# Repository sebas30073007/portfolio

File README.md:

# Portafolio — Sebastián Méndez Villegas (SMV)

Portafolio personal de proyectos de ingeniería mecatrónica y sistemas
ciberfísicos. Hecho con **HTML, CSS y JavaScript** (sin frameworks), listo para
publicar en **GitHub Pages**. Diseño base tomado de `assets/docs/portfolio SMV.pdf`.

## Estructura

```
portfolio/
├── index.html              # Home: feed de proyectos (búsqueda + filtro), sin hero
├── featured-projects.html  # Catálogo premium: Torque, Teleop Mobile Manipulator, Capa8
├── css/
│   └── styles.css          # Sistema de diseño (colores/tipografía en :root)
├── js/
│   ├── data.js              # TODO el contenido editable (catálogo)
│   └── main.js               # Render del feed, modal, filtros y paneles About/Contact
├── assets/
│   ├── img/                # Coloca aquí profile.jpg (foto del hero)
│   └── docs/                # PDF de diseño base
└── README.md
```

About y Contact son secciones al pie de `index.html` (anclas `#about` y
`#contact`). El footer de todas las páginas es la **cartela** SEBS (capa 1,
`brand/chrome.css`): ID, fecha de publicación y estado. Al publicar, actualizar
la fecha de la cartela. Los tokens y el chrome de marca llegan de `brand/`,
que se genera desde la skill `sebs-brand` con `scripts/publish.py` (no editar a mano).

## Editar contenido

Todo el contenido vive en **`js/data.js`**:

- `TIMELINE` — nodos (año + mes opcional) de la línea de tiempo del index.
- `CATALOG` — categorías de la página de proyectos. Cada una tiene `years`, y
  cada año un arreglo de tarjetas `{ title, tag, desc, repo, demo }`.
  Deja `years: {}` para mostrar el estado "próximamente".

## Foto de perfil

Coloca tu foto en `assets/img/profile.jpg`. Si no existe, el hero muestra las
iniciales "SMV" como respaldo (no rompe nada).

## Ver localmente

Abre `index.html` en el navegador, o sirve la carpeta:

```bash
python -m http.server 8000   # luego http://localhost:8000
```

## Publicar en GitHub Pages

1. Sube esta carpeta a un repositorio en GitHub.
2. Settings → Pages → Source: `main` / carpeta raíz (`/`).

## Estado (esta iteración)

Base del diseño replicada. Pendiente para siguientes iteraciones:
- Páginas/modales de detalle por proyecto, paper y competición.
- Visor 3D de ensamble de PCBs (KiCAD → Inventor → STEP/GLB).
- Tarjeta de presentación tipo PCB transparente interactiva en Contact.
- Foto real, textos definitivos y datos de papers/competiciones.

## Enlaces

- GitHub: https://github.com/sebas30073007
- Torke (app en vivo): https://torke.sebs.mx/
- Capa 8 (app en vivo): https://capa8.sebs.mx/
- Capa 8 (open source): https://github.com/sebas30073007/IA_mecatronica_Capa8

> Nota: se corrigieron typos del PDF ("Proyects"→"Projects",
> "arquitectures"→"architectures", etc.) por tratarse de un portafolio público.
> Torke es de código cerrado (sin repo público).

## Medios (peso de la página)

- Imágenes: se publican en `.webp` (portadas a 1600 px, esquemáticos y capas de PCB a 2400 px). Los PNG/JPG originales se conservan al lado, pero ninguna página los pide. Para una imagen nueva pesada, generar su `.webp` y referenciar ese.
- Giros 3D de las tarjetas (`spin` + `poster` en `data.js`): la tarjeta muestra el póster; el video no se precarga y solo gira al pasar el mouse (en táctil se queda el póster). El 3D interactivo vive en el detalle.
- Videos de Featured: versiones recomprimidas en `assets/vid/web/` (con póster); los originales de `assets/vid/` ya no se usan.
- La tarjeta no lleva botones encima: toda ella abre el detalle, y ahí están el enlace externo y «Copy link».

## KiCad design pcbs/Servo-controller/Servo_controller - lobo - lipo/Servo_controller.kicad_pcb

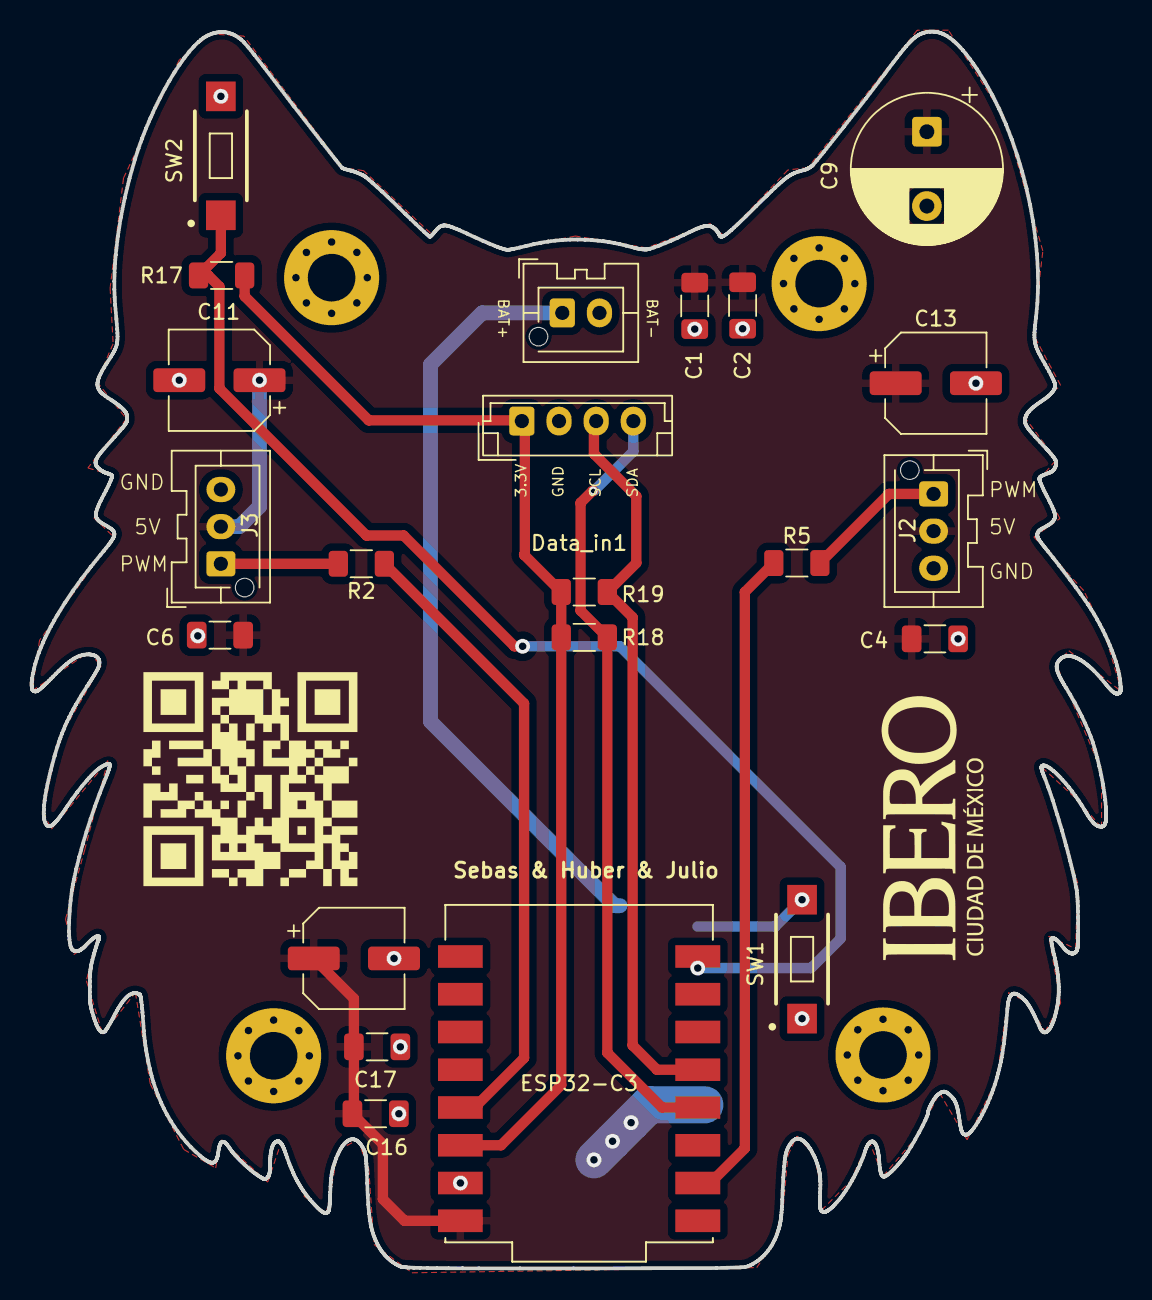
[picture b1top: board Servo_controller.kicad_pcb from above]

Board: 2 copper layers, 73.3 x 83.2 mm, 27 parts (1 on the bottom side), 12 nets.

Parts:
C1, C4, C6, C16: 100nF; C_1206_3216Metric_Pad1.33x1.80mm_HandSolder
C2, C17: 10uF; C_1206_3216Metric_Pad1.33x1.80mm_HandSolder
C9: 1000uF; CP_Radial_D10.0mm_P5.00mm
C11, C13, C18: 470uF; CP_Elec_6.3x7.7
Data_in1: I2C; JST_EH_B4B-EH-A_1x04_P2.50mm_Vertical
ESP32-C3: ESP32-C3_SUPERMINI_SMD; MODULE_ESP32-C3_SUPERMINI
H1, H2, H3, H4: MountingHole_Pad_MP; MountingHole_3.2mm_M3_Pad_Via
J2: Servo 2; JST_XA_B03B-XASK-1-A_1x03_P2.50mm_Vertical
J3: Servo 3; JST_XA_B03B-XASK-1-A_1x03_P2.50mm_Vertical
J5: Conn_01x02_Socket; JST_XA_B02B-XASK-1-A_1x02_P2.50mm_Vertical
LIPO_CHARGER1: MOD_LiPo_USB-C_5V2A_AR3462_25x20mm
R2, R5: 100; R_1206_3216Metric_Pad1.30x1.75mm_HandSolder
R17: 10k; R_1206_3216Metric_Pad1.30x1.75mm_HandSolder
R18, R19: 4.7k; R_1206_3216Metric_Pad1.30x1.75mm_HandSolder
SW1, SW2: SW_Push; SW_RS-032G05A3-SMRT

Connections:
+3.3V: Data_in1.1, ESP32-C3.3.3 (3V3), R17.2, R18.2, R19.2
+5V: C1.1, C2.1, C4.1, C6.1, C9.1, C11.1, C13.1, C16.1, C17.1, C18.1, ESP32-C3.5V, J2.2, J3.2, LIPO_CHARGER1.3 (5V_OUT)
BTN: ESP32-C3.21 (GPIO21), R17.1, SW2.1
GND: C1.2, C2.2, C4.2, C6.2, C9.2, C11.2, C13.2, C16.2, C17.2, C18.2, Data_in1.2, ESP32-C3.G (GND), J2.3, J3.3, J5.2, LIPO_CHARGER1.2 (BAT-_/_GND), LIPO_CHARGER1.4 (GND_OUT), SW1.1, SW2.2
unnamed: ESP32-C3.4 (GPIO4), R2.1
unnamed: ESP32-C3.6 (GPIO6), R5.1
unnamed: LIPO_CHARGER1.5 (Key), SW1.2
PWM_2: J2.1, R5.2
PWM_3: J3.1, R2.2
SCL: Data_in1.3, ESP32-C3.9 (GPIO9), R19.1
SDA: Data_in1.4, ESP32-C3.8 (GPIO8), R18.1
Vcc: J5.1, LIPO_CHARGER1.1 (BAT+)

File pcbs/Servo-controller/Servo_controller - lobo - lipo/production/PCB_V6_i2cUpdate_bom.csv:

Designator,Footprint,Quantity,Value,LCSC Part #
"C1, C16, C4, C6",1206,4,100nF,
"C11, C13, C18",CP_Elec_6.3x7.7,3,470uF,
"C17, C2",1206,2,10uF,
C9,CP_Radial_D10.0mm_P5.00mm,1,1000uF,
DATA_IN1,JST_EH_B4B-EH-A_1x04_P2.50mm_Vertical,1,I2C,
ESP32-C3,MODULE_ESP32-C3_SUPERMINI,1,ESP32-C3_SUPERMINI_SMD,
J2,JST_XA_B03B-XASK-1-A_1x03_P2.50mm_Vertical,1,Servo 2,
J3,JST_XA_B03B-XASK-1-A_1x03_P2.50mm_Vertical,1,Servo 3,
J5,JST_XA_B02B-XASK-1-A_1x02_P2.50mm_Vertical,1,Conn_01x02_Socket,
LIPO_CHARGER1,MOD_LiPo_USB-C_5V2A_AR3462_25x20mm,1,~,
R17,1206,1,10k,
"R18, R19",1206,2,4.7k,
"R2, R5",1206,2,100,
"SW1, SW2",SW_RS-032G05A3-SMRT,2,SW_Push,

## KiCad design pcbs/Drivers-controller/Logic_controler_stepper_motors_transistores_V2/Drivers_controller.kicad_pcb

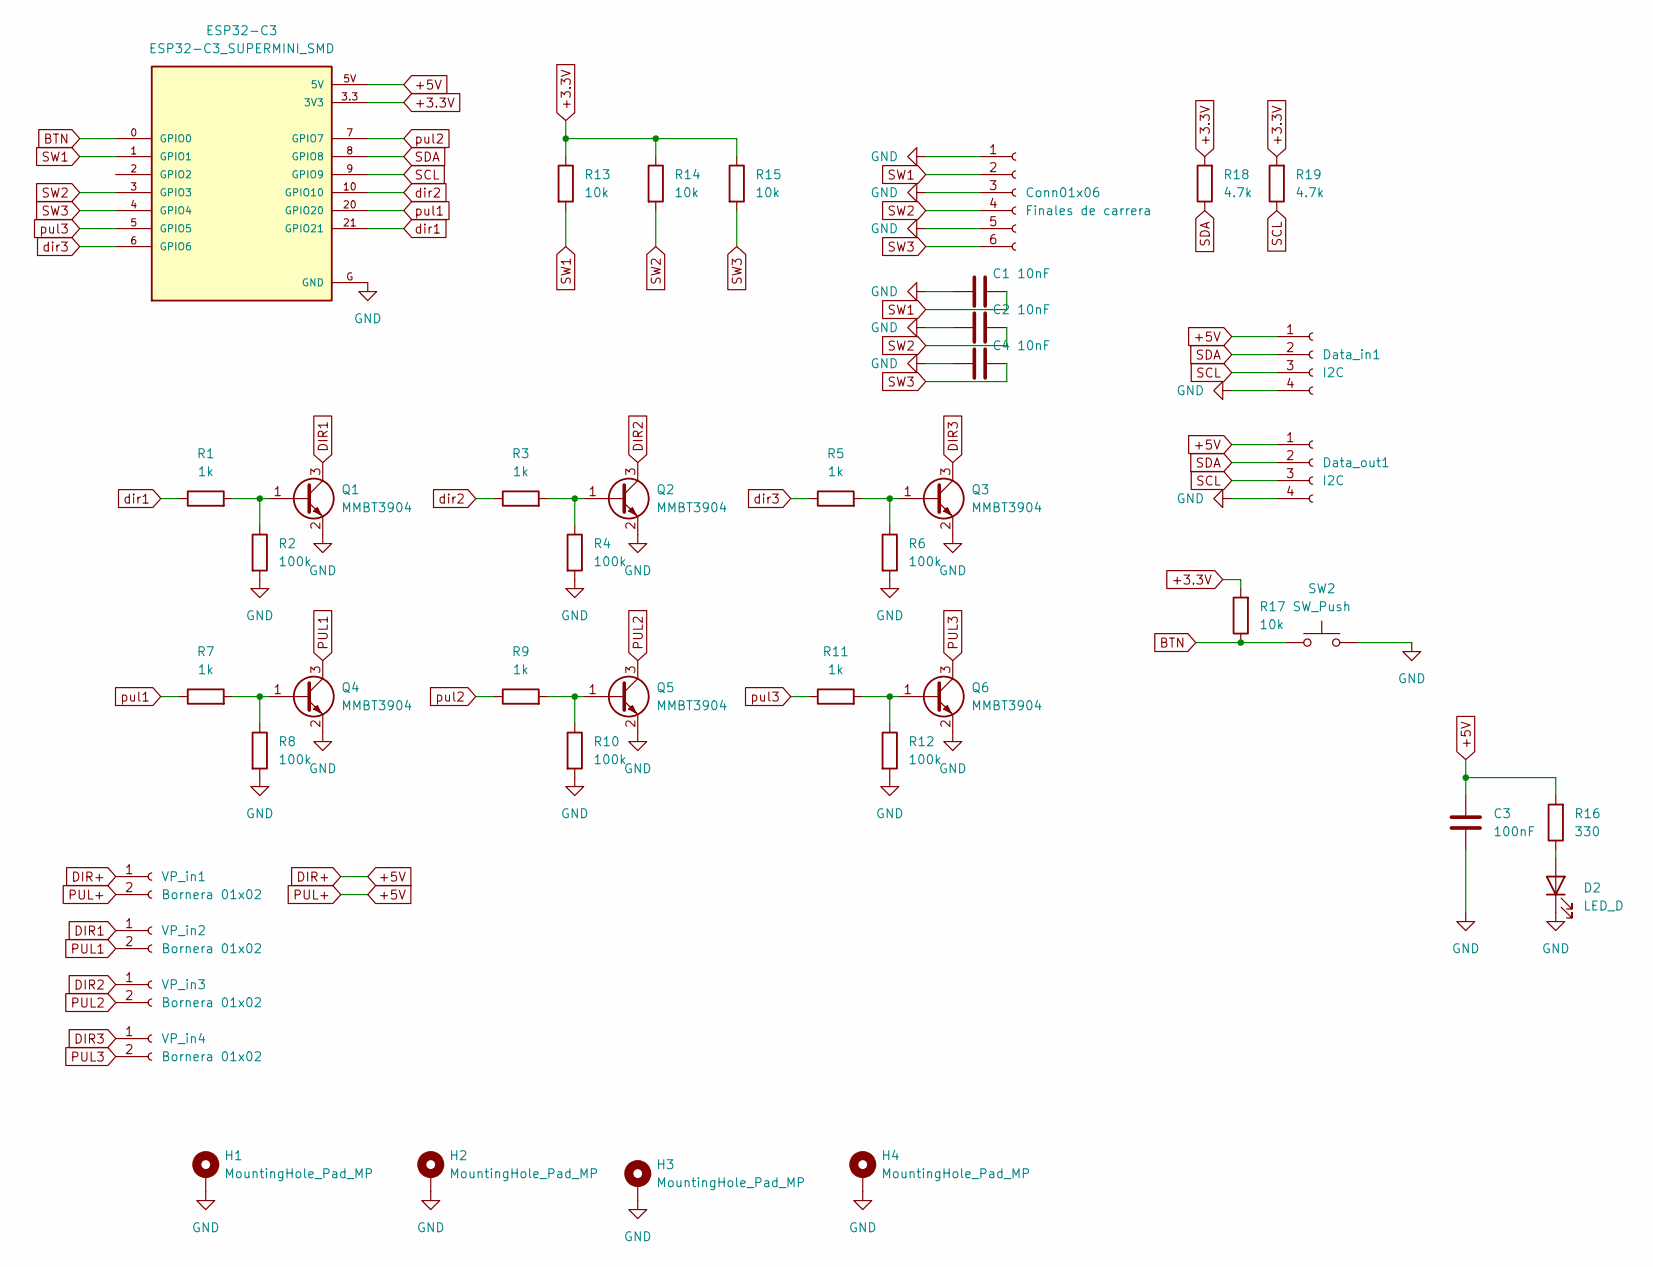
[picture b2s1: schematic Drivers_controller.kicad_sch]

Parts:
C1, C2, C4: 10nF; C_1206_3216Metric_Pad1.33x1.80mm_HandSolder
C3: 100nF; C_1206_3216Metric_Pad1.33x1.80mm_HandSolder
Conn01x06: Finales de carrera; JST_EH_B6B-EH-A_1x06_P2.50mm_Vertical
D2: LED_D; LED_1206_3216Metric
Data_in1: I2C; JST_EH_B4B-EH-A_1x04_P2.50mm_Vertical
Data_out1: I2C; JST_EH_B4B-EH-A_1x04_P2.50mm_Vertical
ESP32-C3: ESP32-C3_SUPERMINI_SMD; MODULE_ESP32-C3_SUPERMINI
H1, H2, H3, H4: MountingHole_Pad_MP; MountingHole_3.2mm_M3_Pad_Via
Q1, Q2, Q3, Q4, Q5, Q6: MMBT3904; SOT-23_Handsoldering
R1, R3, R5, R7, R9, R11: 1k; R_1206_3216Metric_Pad1.30x1.75mm_HandSolder
R2, R4, R6, R8, R10, R12: 100k; R_1206_3216Metric_Pad1.30x1.75mm_HandSolder
R13, R14, R15, R17: 10k; R_1206_3216Metric_Pad1.30x1.75mm_HandSolder
R16: 330; R_1206_3216Metric_Pad1.30x1.75mm_HandSolder
R18, R19: 4.7k; R_1206_3216Metric_Pad1.30x1.75mm_HandSolder
SW2: SW_Push; SW_RS-032G05A3-SMRT
VP_in1, VP_in2, VP_in3, VP_in4: Bornera 01x02; TerminalBlock_MaiXu_MX126-5.0-02P_1x02_P5.00mm

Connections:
+3.3V: ESP32-C3.3.3 (3V3), R13.1, R14.1, R15.1, R17.2, R18.2, R19.2
+5V: C3.1, Data_in1.1, Data_out1.1, ESP32-C3.5V, R16.2, VP_in1.1, VP_in1.2
BTN: ESP32-C3.0 (GPIO0), R17.1, SW2.1
DIR1: Q1.3 (C), VP_in2.1
DIR2: Q2.3 (C), VP_in3.1
DIR3: Q3.3 (C), VP_in4.1
GND: C1.1, C2.1, C3.2, C4.1, Conn01x06.1, Conn01x06.3, Conn01x06.5, D2.1 (K), Data_in1.4, Data_out1.4, ESP32-C3.G (GND), H1.MP, H2.MP, H3.MP, H4.MP, Q1.2 (E), Q2.2 (E), Q3.2 (E), Q4.2 (E), Q5.2 (E), Q6.2 (E), R2.2, R4.2, R6.2, R8.2, R10.2, R12.2, SW2.2
unnamed: D2.2 (A), R16.1
unnamed: Q1.1 (B), R1.2, R2.1
unnamed: Q2.1 (B), R3.2, R4.1
unnamed: Q3.1 (B), R5.2, R6.1
unnamed: Q4.1 (B), R7.2, R8.1
unnamed: Q5.1 (B), R9.2, R10.1
unnamed: Q6.1 (B), R11.2, R12.1
PUL1: Q4.3 (C), VP_in2.2
PUL2: Q5.3 (C), VP_in3.2
PUL3: Q6.3 (C), VP_in4.2
SCL: Data_in1.3, Data_out1.3, ESP32-C3.9 (GPIO9), R19.1
SDA: Data_in1.2, Data_out1.2, ESP32-C3.8 (GPIO8), R18.1
SW1: C1.2, Conn01x06.2, ESP32-C3.1 (GPIO1), R13.2
SW2: C2.2, Conn01x06.4, ESP32-C3.3 (GPIO3), R14.2
SW3: C4.2, Conn01x06.6, ESP32-C3.4 (GPIO4), R15.2
dir1: ESP32-C3.21 (GPIO21), R1.1
dir2: ESP32-C3.10 (GPIO10), R3.1
dir3: ESP32-C3.6 (GPIO6), R5.1
pul1: ESP32-C3.20 (GPIO20), R7.1
pul2: ESP32-C3.7 (GPIO7), R9.1
pul3: ESP32-C3.5 (GPIO5), R11.1

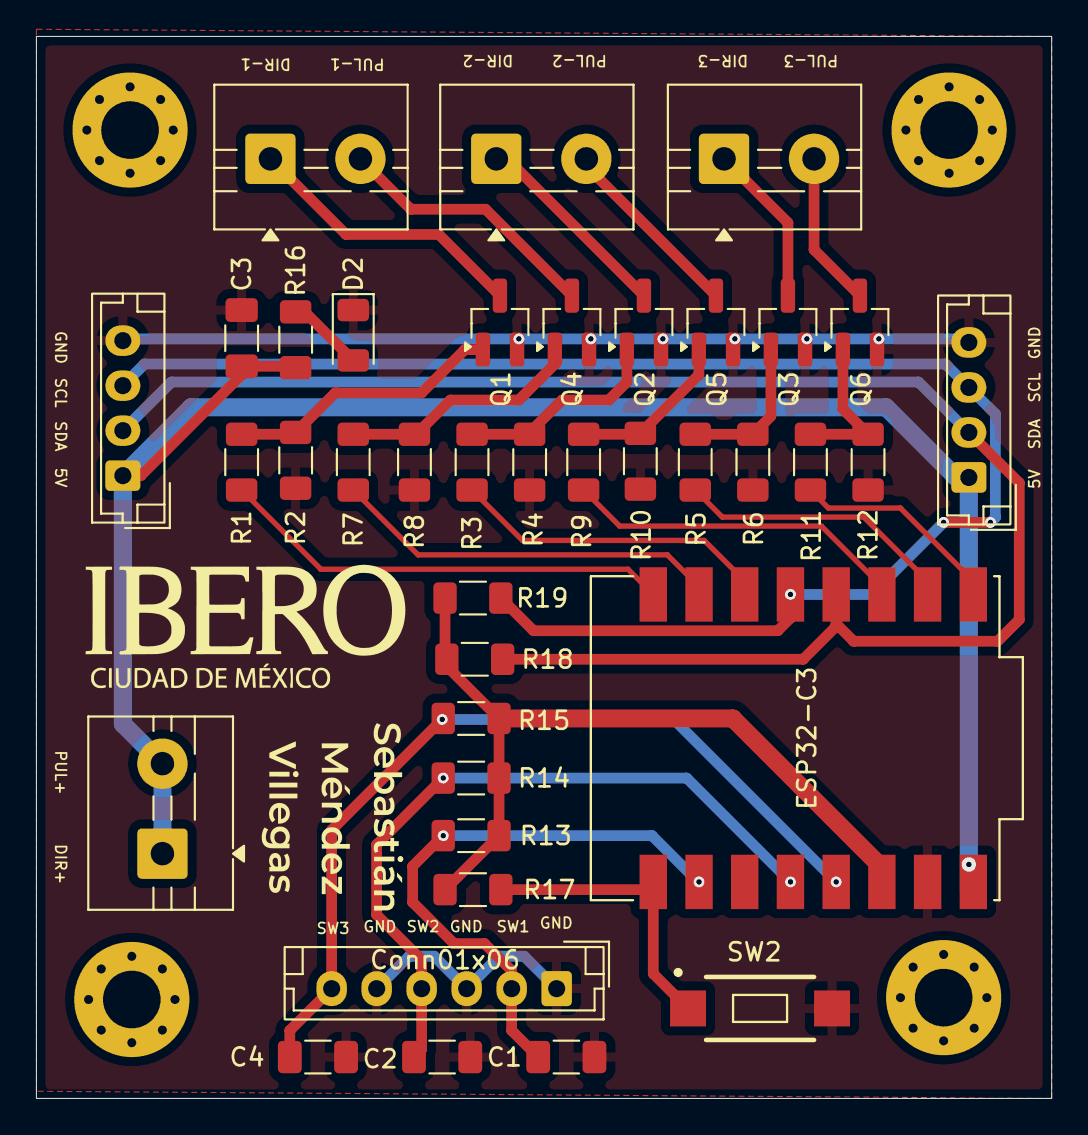
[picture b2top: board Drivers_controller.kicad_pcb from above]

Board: 2 copper layers, 56.4 x 59.0 mm, 43 parts (0 on the bottom side), 28 nets.

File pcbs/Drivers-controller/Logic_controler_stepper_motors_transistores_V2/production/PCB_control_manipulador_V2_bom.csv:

Designator,Footprint,Quantity,Value,LCSC Part #
"C1, C2, C4",1206,3,10nF,
C3,1206,1,100nF,
CONN01X06,JST_EH_B6B-EH-A_1x06_P2.50mm_Vertical,1,Finales de carrera,
D2,1206,1,LED_D,
"DATA_IN1, DATA_OUT1",JST_EH_B4B-EH-A_1x04_P2.50mm_Vertical,2,I2C,
ESP32-C3,MODULE_ESP32-C3_SUPERMINI,1,ESP32-C3_SUPERMINI_SMD,
"Q1, Q2, Q3, Q4, Q5, Q6",SOT-23_Handsoldering,6,MMBT3904,
"R1, R11, R3, R5, R7, R9",1206,6,1k,
"R10, R12, R2, R4, R6, R8",1206,6,100k,
"R13, R14, R15, R17",1206,4,10k,
R16,1206,1,330,
"R18, R19",1206,2,4.7k,
SW2,SW_RS-032G05A3-SMRT,1,SW_Push,
"VP_IN1, VP_IN2, VP_IN3, VP_IN4",TerminalBlock_MaiXu_MX126-5.0-02P_1x02_P5.00mm,4,Bornera 01x02,

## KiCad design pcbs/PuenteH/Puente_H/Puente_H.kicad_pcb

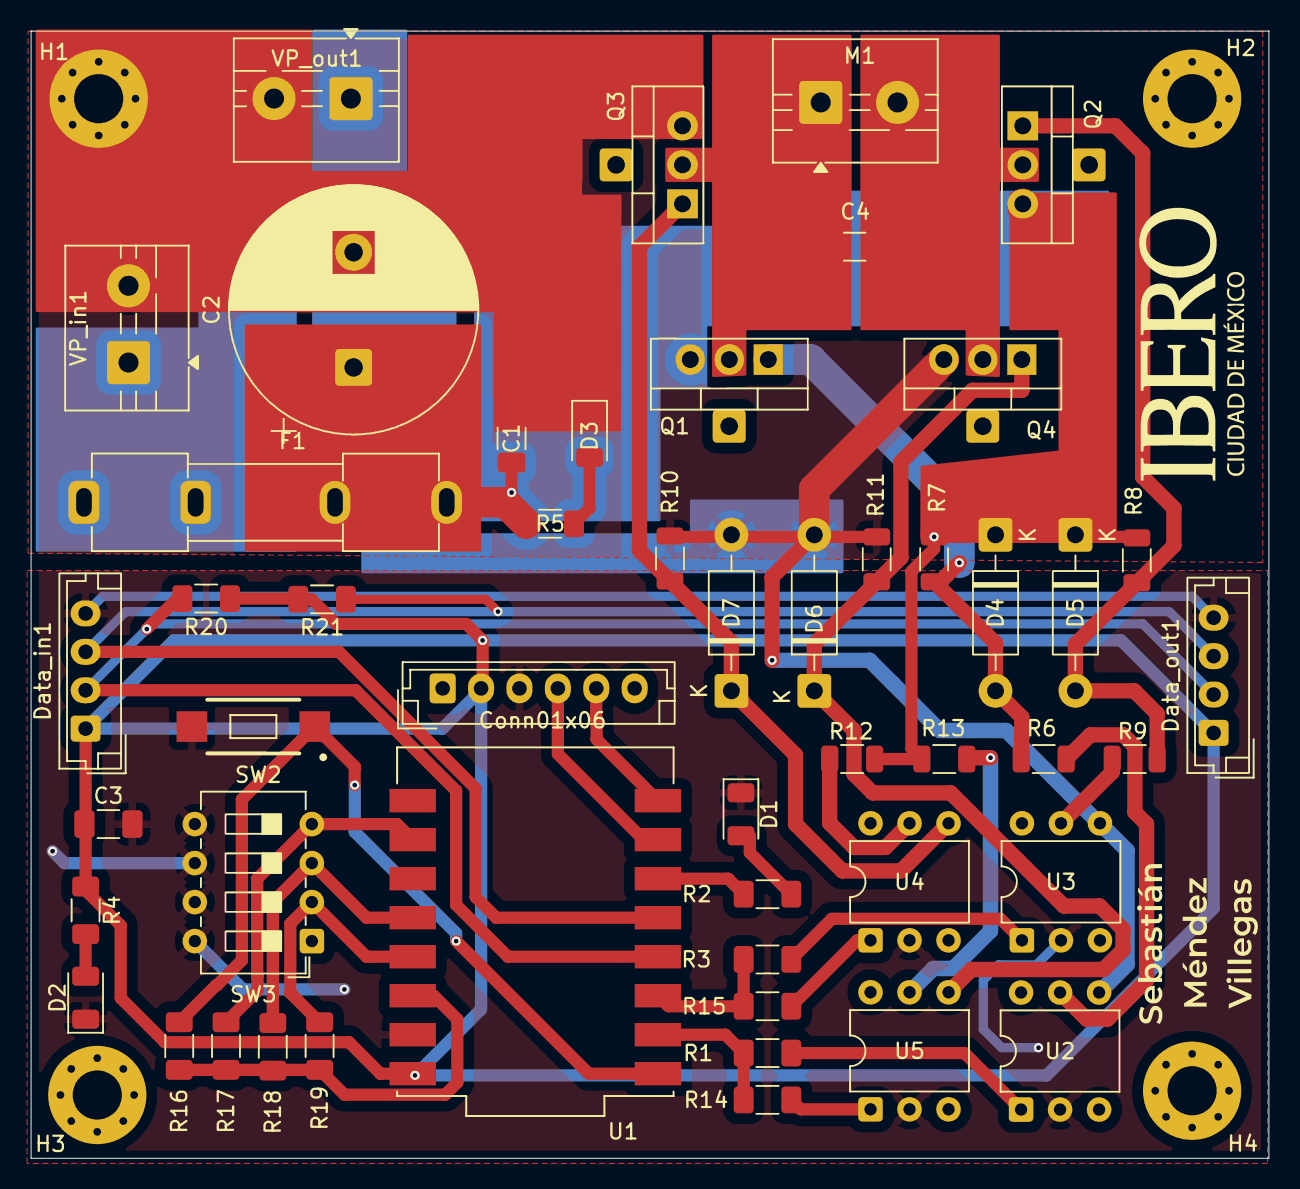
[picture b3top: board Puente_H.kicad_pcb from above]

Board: 2 copper layers, 80.6 x 73.4 mm, 58 parts (0 on the bottom side), 34 nets.

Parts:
C1, C3, C4: 100nF; C_1206_3216Metric_Pad1.33x1.80mm_HandSolder
C2: 2200uF 50V; CP_Radial_D16.0mm_P7.50mm
Conn01x06: HC-05; JST_EH_B6B-EH-A_1x06_P2.50mm_Vertical
D1: LED; LED_1206_3216Metric
D2: LED_D; LED_1206_3216Metric
D3: LED_P; LED_1206_3216Metric
D4, D5, D6, D7: 1N47xxA; D_DO-41_SOD81_P10.16mm_Horizontal
Data_in1: I2C; JST_EH_B4B-EH-A_1x04_P2.50mm_Vertical
Data_out1: I2C; JST_EH_B4B-EH-A_1x04_P2.50mm_Vertical
F1: Fuse; Fuseholder_Clip-5x20mm_Keystone_3512_Inline_P23.62x7.27mm_D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
H1, H2, H3, H4: MountingHole_Pad_MP; MountingHole_3.2mm_M3_Pad_Via
J1, J2, J3, J4: Conn_01x01_Pin; SolderWire-0.5sqmm_1x01_D0.9mm_OD2.1mm
M1: Motor_DC; TerminalBlock_MaiXu_MX126-5.0-02P_1x02_P5.00mm
Q1, Q2: IRF9540N; TO-220-3_Vertical
Q3, Q4: IRF540N; TO-220-3_Vertical
R1, R2, R3, R4, R14, R15: 330; R_1206_3216Metric_Pad1.30x1.75mm_HandSolder
R5: 3.3k; R_1206_3216Metric_Pad1.30x1.75mm_HandSolder
R6, R9, R12, R13: 2.2k; R_1206_3216Metric
R7, R8, R10, R11: 10k; R_1206_3216Metric
R16, R17, R18, R19: 10k; R_1206_3216Metric_Pad1.30x1.75mm_HandSolder
R20, R21: 4.7k; R_1206_3216Metric_Pad1.30x1.75mm_HandSolder
SW2: SW_Push; SW_RS-032G05A3-SMRT
SW3: Dip_Switch_04; SW_DIP_SPSTx04_Slide_6.7x11.72mm_W7.62mm_P2.54mm_LowProfile
U1: ESP32-C3_SUPERMINI_SMD; MODULE_ESP32-C3_SUPERMINI
U2, U3, U4, U5: 4N25; DIP-6_W7.62mm
VP_in1: Conn_01x02; TerminalBlock_MaiXu_MX126-5.0-02P_1x02_P5.00mm
VP_out1: Conn_01x02; TerminalBlock_MaiXu_MX126-5.0-02P_1x02_P5.00mm

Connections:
+3.3V: R16.2, R17.2, R18.2, R19.2, U1.3.3 (3V3)
+5V: C3.1, Conn01x06.2, Data_in1.1, Data_out1.1, R4.2, R20.2, R21.2, U1.5V
+24V: F1.1, VP_in1.1, VP_out1.1
BTN: R16.1, SW2.1, U1.5 (GPIO5)
GND: C3.2, Conn01x06.3, D1.1 (K), D2.1 (K), Data_in1.4, Data_out1.4, SW2.2, SW3.5, SW3.6, SW3.7, SW3.8, U1.G (GND), U2.2, U3.2, U4.2, U5.2
GNDPWR: C1.2, C2.2, D3.1 (K), D6.2 (A), D7.2 (A), Q3.3 (S), Q4.3 (S), R10.2, R11.1, U2.4, U3.4, VP_in1.2, VP_out1.2
LED: R2.2, U1.10 (GPIO10)
unnamed: D1.2 (A), R2.1
unnamed: D2.2 (A), R4.1
unnamed: D3.2 (A), R5.1
unnamed: D4.2 (A), Q1.1 (G), R6.2, R7.1
unnamed: D5.2 (A), Q2.1 (G), R8.2, R9.1
unnamed: D6.1 (K), Q4.1 (G), R11.2, U5.4
unnamed: D7.1 (K), Q3.1 (G), R10.1, U4.4
unnamed: C4.2, M1.1 (+), Q1.2 (D), Q3.2 (D)
unnamed: C4.1, M1.2 (-), Q2.2 (D), Q4.2 (D)
unnamed: R1.1, U2.1
unnamed: R3.1, U3.1
unnamed: R6.1, U2.5
unnamed: R9.2, U3.5
unnamed: R12.1, U4.5
unnamed: R13.1, U5.5
unnamed: R14.1, U5.1
unnamed: R15.2, U4.1
PWM_0: R1.2, R14.2, U1.6 (GPIO6)
PWM_1: R3.2, R15.1, U1.7 (GPIO7)
RX: Conn01x06.4, U1.20 (GPIO20)
S0: R17.1, SW3.4, U1.1 (GPIO1)
S1: R18.1, SW3.3, U1.3 (GPIO3)
S2: R19.1, SW3.2, U1.4 (GPIO4)
SCL: Data_in1.3, Data_out1.3, R21.1, U1.9 (GPIO9)
SDA: Data_in1.2, Data_out1.2, R20.1, U1.8 (GPIO8)
TX: Conn01x06.5, U1.21 (GPIO21)
VP: C1.1, C2.1, D4.1 (K), D5.1 (K), F1.2, Q1.3 (S), Q2.3 (S), R5.2, R7.2, R8.1, R12.2, R13.2
